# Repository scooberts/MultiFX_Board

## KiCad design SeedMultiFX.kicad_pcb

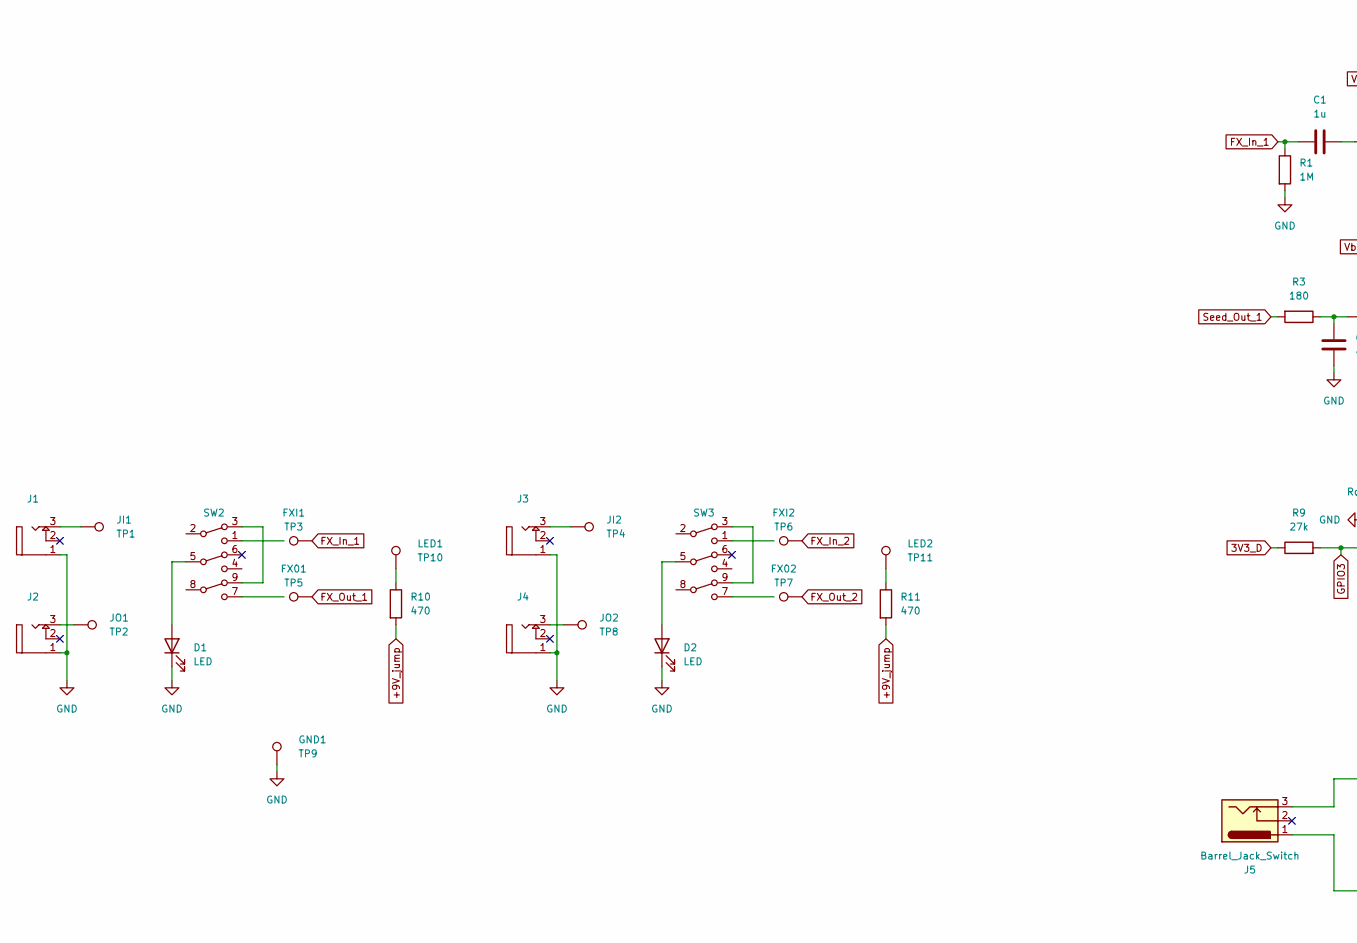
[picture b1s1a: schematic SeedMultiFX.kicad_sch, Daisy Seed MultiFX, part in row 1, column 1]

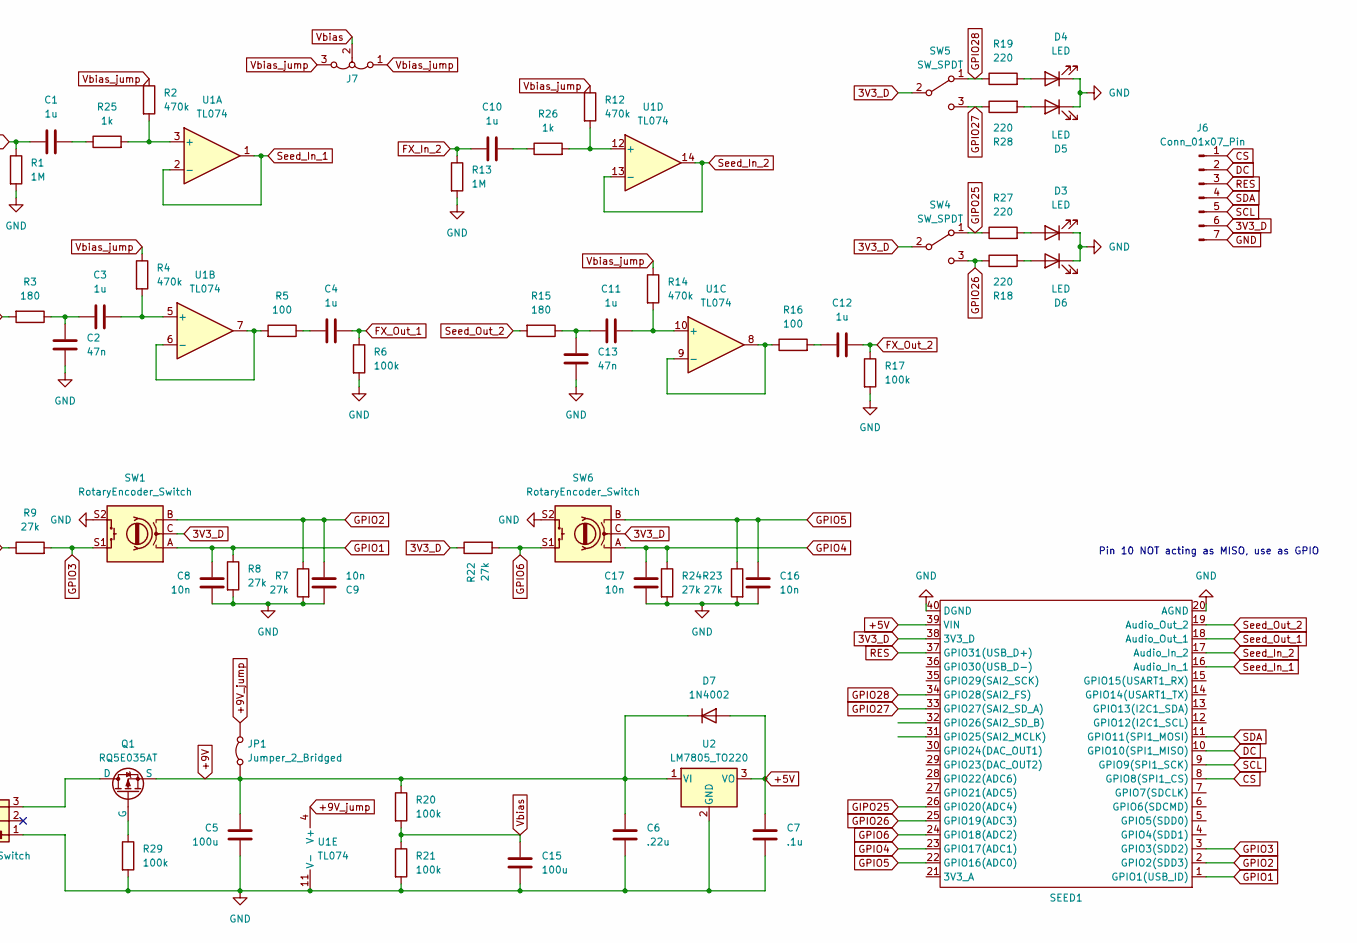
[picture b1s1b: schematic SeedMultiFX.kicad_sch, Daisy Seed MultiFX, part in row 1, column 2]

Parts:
C1, C3, C4, C10, C11, C12: 1u; C_Radial_D5.0mm_H11.0mm_P2.00mm
C2, C13: 47n; C_Rect_L7.2mm_W2.5mm_P5.00mm_FKS2_FKP2_MKS2_MKP2
C5, C15: 100u; C_Radial_D6.3mm_H11.0mm_P2.50mm
C6: .22u; C_Rect_L7.2mm_W3.5mm_P5.00mm_FKS2_FKP2_MKS2_MKP2
C7: .1u; C_Rect_L7.2mm_W2.5mm_P5.00mm_FKS2_FKP2_MKS2_MKP2
C8, C9, C16, C17: 10n; C_Disc_D3.0mm_W1.6mm_P2.50mm
D1, D2, D3, D4, D5, D6: LED; LED_D3.0mm
D7: 1N4002; D_DO-41_SOD81_P7.62mm_Horizontal
FX01: TP5; Plated Hole
FX02: TP7; Plated Hole
FXI1: TP3; Plated Hole
FXI2: TP6; Plated Hole
GND1: TP9; Plated Hole
J1, J2, J3, J4: TaydaFemaleJack
J5: Barrel_Jack_Switch; DCPower2.1mm
J6: Conn_01x07_Pin; PinSocket_1x07_P2.54mm_Vertical
J7: Jumper3
JI1: TP1; Plated Hole
JI2: TP4; Plated Hole
JO1: TP2; Plated Hole
JO2: TP8; Plated Hole
JP1: Jumper_2_Bridged; Jumper
LED1: TP10; Plated Hole
LED2: TP11; Plated Hole
Q1: RQ5E035AT; SOT-23_Handsoldering
R1, R13: 1M; R_Axial_DIN0207_L6.3mm_D2.5mm_P7.62mm_Horizontal
R2, R4, R12, R14: 470k; R_Axial_DIN0207_L6.3mm_D2.5mm_P7.62mm_Horizontal
R3, R15: 180; R_Axial_DIN0207_L6.3mm_D2.5mm_P7.62mm_Horizontal
R5, R16: 100; R_Axial_DIN0207_L6.3mm_D2.5mm_P7.62mm_Horizontal
R6, R17, R20, R21, R29: 100k; R_Axial_DIN0207_L6.3mm_D2.5mm_P7.62mm_Horizontal
R7, R8, R9, R22, R23, R24: 27k; R_Axial_DIN0204_L3.6mm_D1.6mm_P5.08mm_Horizontal
R10, R11: 470; R_Axial_DIN0207_L6.3mm_D2.5mm_P7.62mm_Horizontal
R18, R19, R27, R28: 220; R_Axial_DIN0207_L6.3mm_D2.5mm_P7.62mm_Horizontal
R25, R26: 1k; R_Axial_DIN0207_L6.3mm_D2.5mm_P7.62mm_Horizontal
SEED1: Electrosmith_Daisy_Seed
SW1, SW6: RotaryEncoder_Switch; Quadrature Encoder
SW2, SW3: 3PDT Interface
SW4, SW5: SW_SPDT; SPDT_MiniToggle
U1: TL074; DIP-14_W7.62mm
U2: LM7805_TO220; TO-220-3_Vertical

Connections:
3V3_D: J6.6, R9.1, R22.1, SEED1.38 (3V3_D), SW1.C, SW4.2 (B), SW5.2 (B), SW6.C
+5V: C7.1, D7.2 (A), SEED1.39 (VIN), U2.3 (VO)
+9V: C5.1, C6.1, D7.1 (K), JP1.1 (A), Q1.3 (S), R20.1, U2.1 (VI)
+9V_jump: JP1.2 (B), R10.2, R11.2, U1.4 (V+)
CS: J6.1, SEED1.8 (GPIO8(SPI1_CS))
DC: J6.2, SEED1.10 (GPIO10(SPI1_MISO))
FX_In_1: C1.1, FXI1.1, R1.1
FX_In_2: C10.1, FXI2.1, R13.1
FX_Out_1: C4.2, FX01.1, R6.1
FX_Out_2: C12.2, FX02.1, R17.1
GIPO25: R27.1, SEED1.26 (GPIO20(ADC4)), SW4.1 (A)
GND: C2.1, C5.2, C6.2, C7.2, C8.2, C9.1, C13.1, C15.2, C16.2, C17.2, D1.1 (K), D2.1 (K), D3.1 (K), D4.1 (K), D5.1 (K), D6.1 (K), GND1.1, J1.1 (2), J2.1 (2), J3.1 (2), J4.1 (2), J5.1, J6.7, R1.2, R6.2, R7.2, R8.2, R13.2, R17.2, R21.2, R23.2, R24.2, R29.2, SEED1.20 (AGND), SEED1.40 (DGND), SW1.S2, SW6.S2, U1.11 (V-), U2.2 (GND)
GPIO1: C8.1, R8.1, SEED1.1 (GPIO1(USB_ID)), SW1.A
GPIO2: C9.2, R7.1, SEED1.2 (GPIO2(SDD3)), SW1.B
GPIO3: R9.2, SEED1.3 (GPIO3(SDD2)), SW1.S1
GPIO4: C17.1, R24.1, SEED1.23 (GPIO17(ADC1)), SW6.A
GPIO5: C16.1, R23.1, SEED1.22 (GPIO16(ADC0)), SW6.B
GPIO6: R22.2, SEED1.24 (GPIO18(ADC2)), SW6.S1
GPIO26: R18.1, SEED1.25 (GPIO19(ADC3)), SW4.3 (C)
GPIO27: R28.1, SEED1.33 (GPIO27(SAI2_SD_A)), SW5.3 (C)
GPIO28: R19.1, SEED1.34 (GPIO28(SAI2_FS)), SW5.1 (A)
unnamed: C1.2, R25.1
unnamed: C2.2, C3.1, R3.1
unnamed: C4.1, R5.1
unnamed: C10.2, R26.1
unnamed: C11.1, C13.2, R15.1
unnamed: C12.1, R16.2
unnamed: D1.2 (A), SW2.5 (B2)
unnamed: D2.2 (A), SW3.5 (B2)
unnamed: D3.2 (A), R27.2
unnamed: D4.2 (A), R19.2
unnamed: D5.2 (A), R28.2
unnamed: D6.2 (A), R18.2
unnamed: J1.3 (1), JI1.1
unnamed: J2.3 (1), JO1.1
unnamed: J3.3 (1), JI2.1
unnamed: J4.3 (1), JO2.1
unnamed: LED1.1, R10.1
unnamed: LED2.1, R11.1
unnamed: J5.3, Q1.1 (D)
unnamed: Q1.2 (G), R29.1
unnamed: SW2.3 (A1), SW2.9 (A3)
unnamed: SW3.3 (A1), SW3.9 (A3)
unnamed: R2.2, R25.2, U1.3 (+)
unnamed: C3.2, R4.2, U1.5 (+)
unnamed: R5.2, U1.6 (-), U1.7
unnamed: C11.2, R14.2, U1.10 (+)
unnamed: R16.1, U1.8, U1.9 (-)
unnamed: R12.2, R26.2, U1.12 (+)
RES: J6.3, SEED1.37 (GPIO31(USB_D+))
SCL: J6.5, SEED1.9 (GPIO9(SPI1_SCK))
SDA: J6.4, SEED1.11 (GPIO11(SPI1_MOSI))
Seed_In_1: SEED1.16 (Audio_In_1), U1.1, U1.2 (-)
Seed_In_2: SEED1.17 (Audio_In_2), U1.13 (-), U1.14
Seed_Out_1: R3.2, SEED1.18 (Audio_Out_1)
Seed_Out_2: R15.2, SEED1.19 (Audio_Out_2)
Vbias: C15.1, J7.2 (C), R20.2, R21.1
Vbias_jump: J7.1 (A), J7.3 (B), R2.1, R4.1, R12.1, R14.1

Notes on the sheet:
Pin 10 NOT acting as MISO, use as GPIO

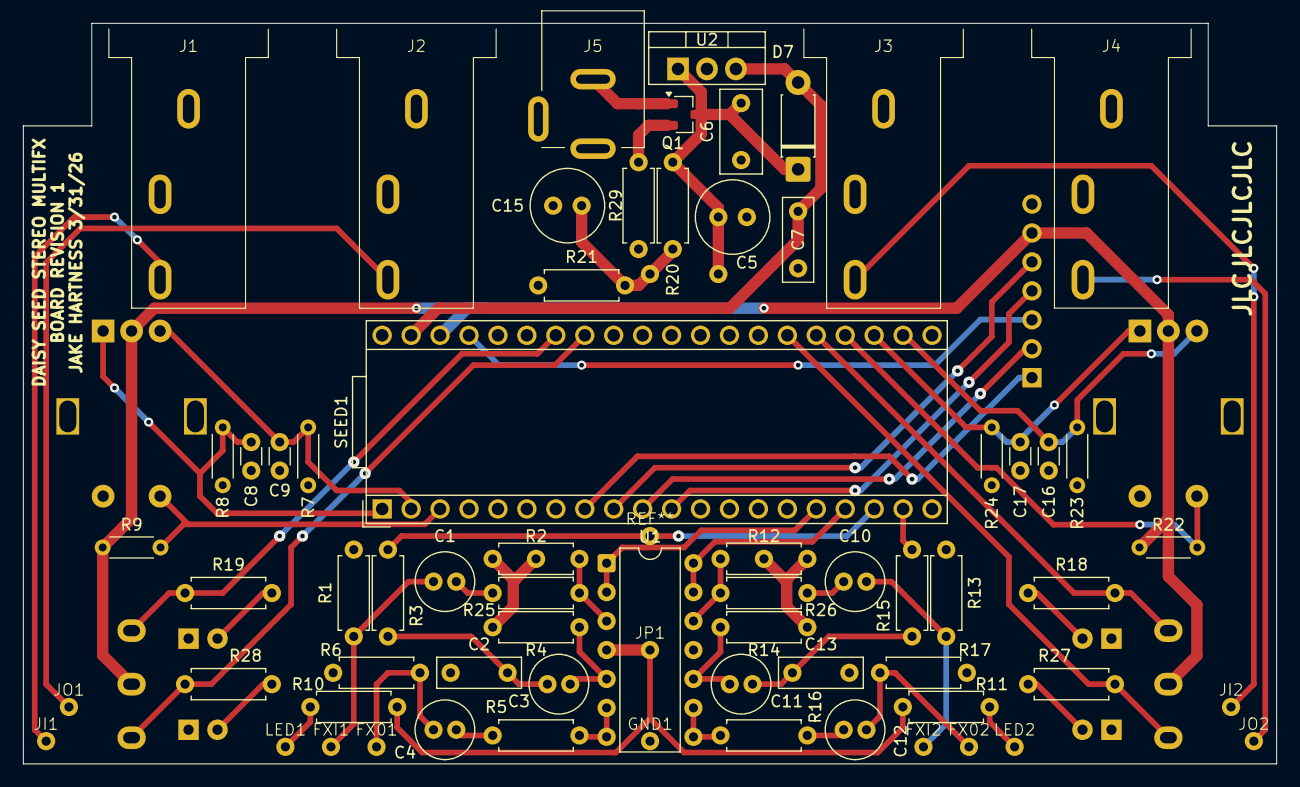
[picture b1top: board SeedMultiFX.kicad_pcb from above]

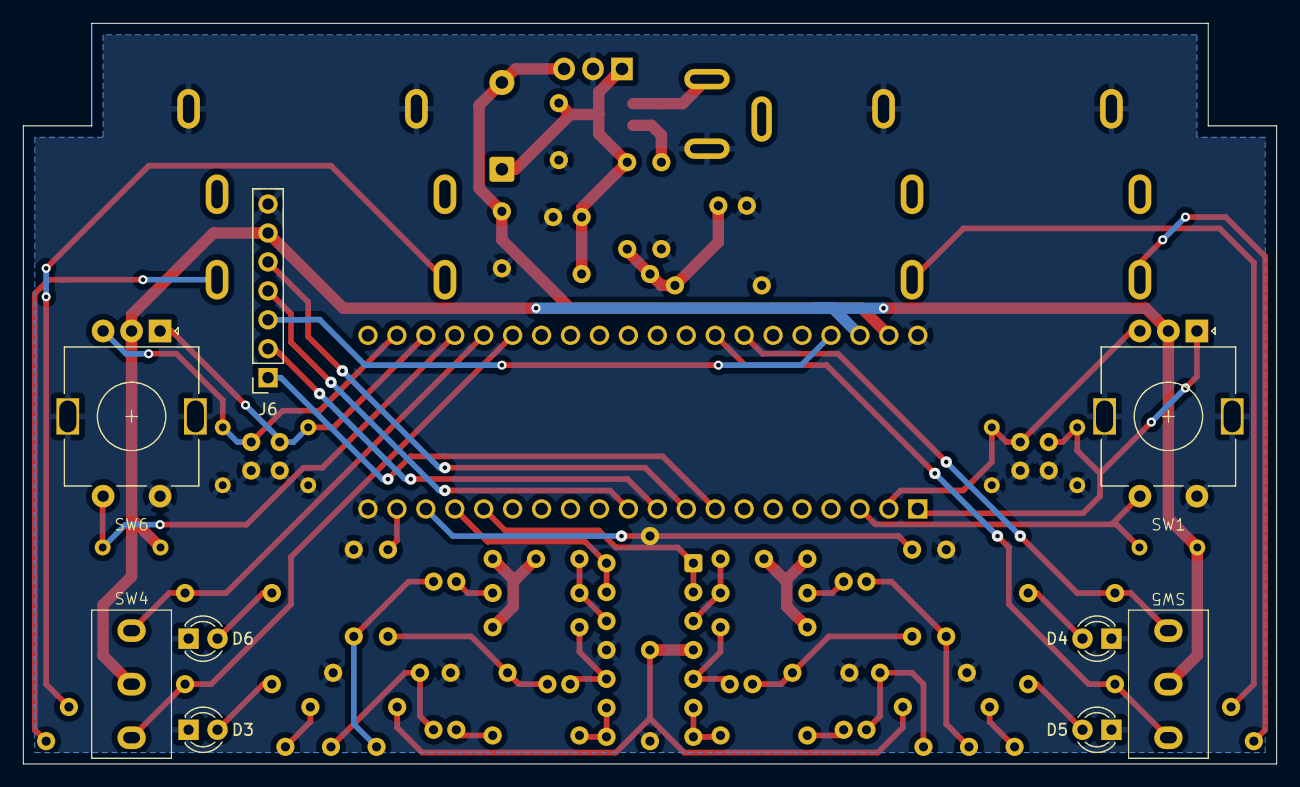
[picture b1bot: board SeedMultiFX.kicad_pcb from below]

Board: 2 copper layers, 110.0 x 65.0 mm, 77 parts (9 on the bottom side), 54 nets.
